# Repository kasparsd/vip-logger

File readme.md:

# Voltage, Current and Power Logger for Electric Skateboards, Scooters and Bicycles

See [the wiki](https://github.com/kasparsd/vip-logger/wiki).

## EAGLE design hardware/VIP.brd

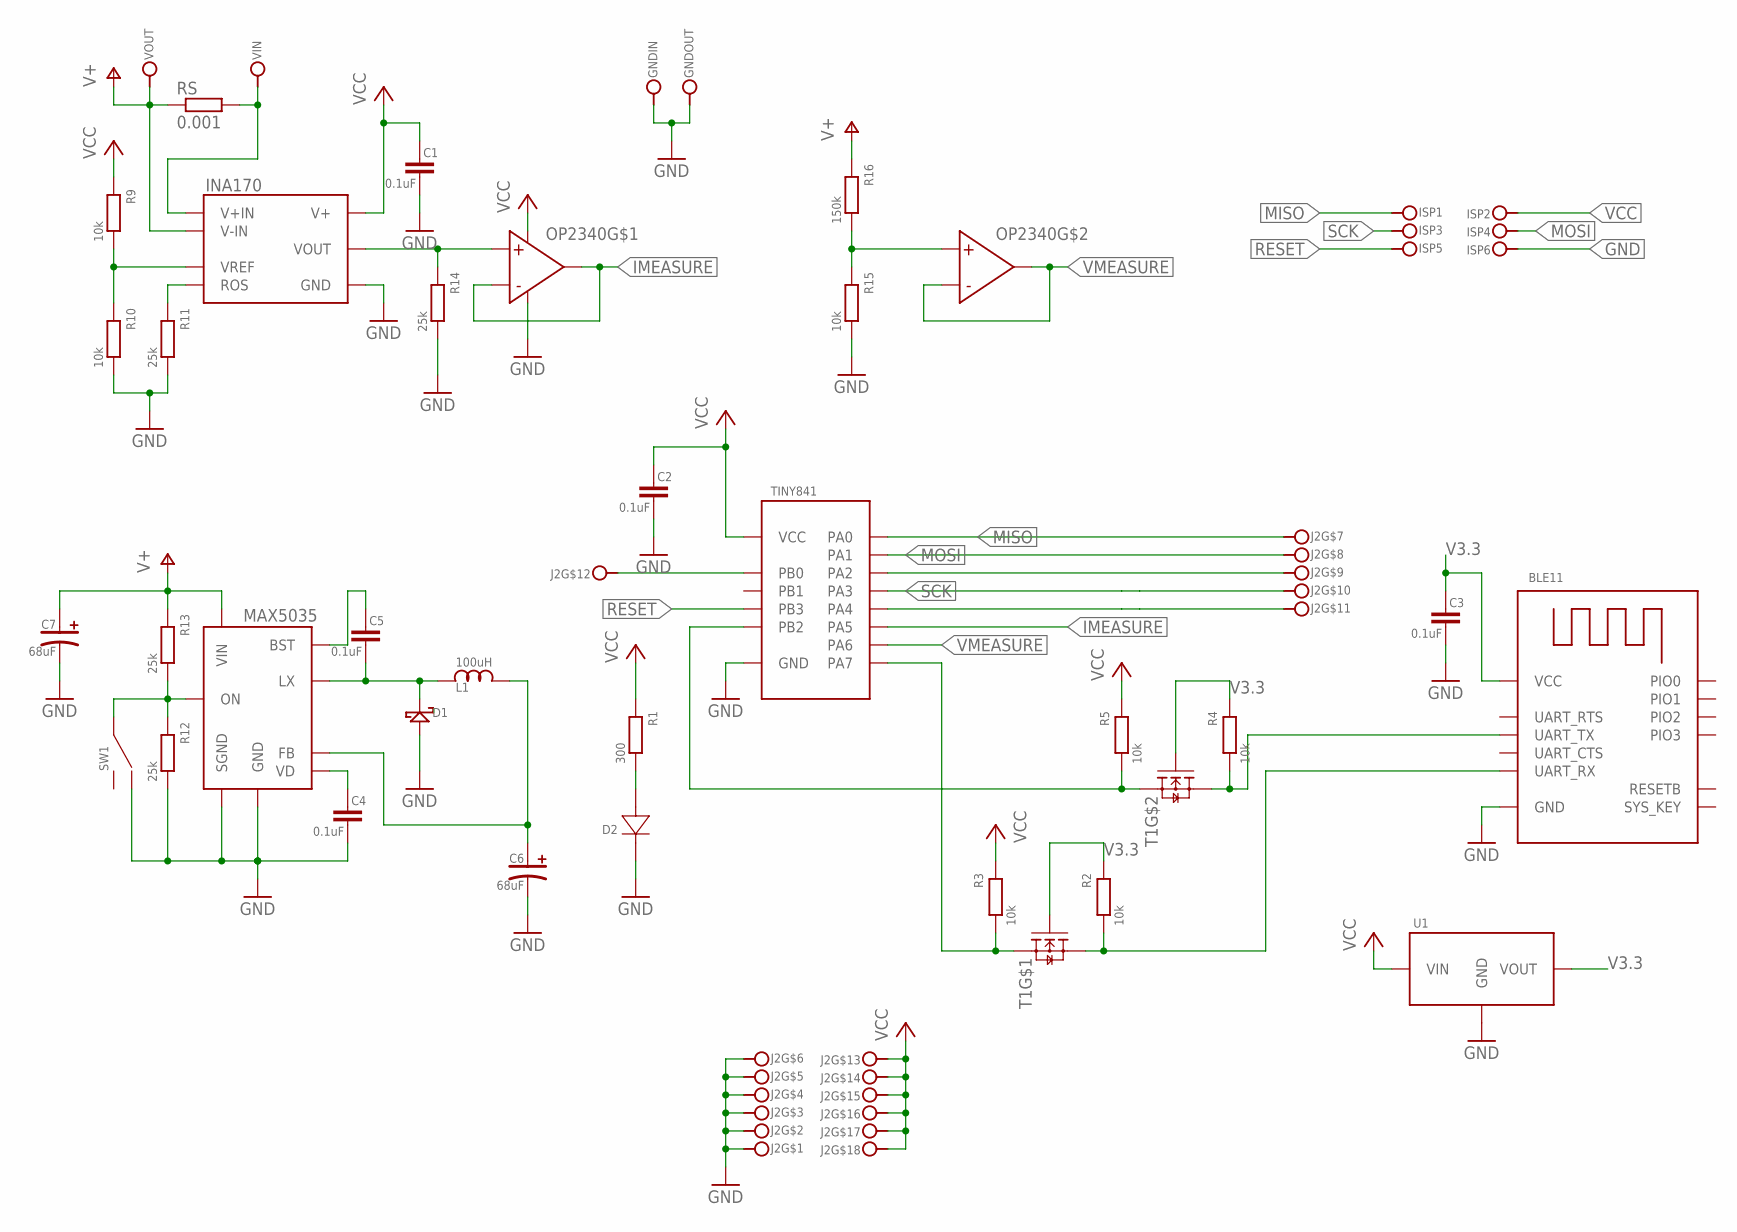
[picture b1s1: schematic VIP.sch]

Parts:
BLE11: HM-17BLE; HM17BLE
C1, C2, C3, C4, C5: 0.1uF; 0603L
C6: 68uF; RAD6.3MM
C7: 68uF; RAD12.5MM
D1: SCHOTTKY; DO-214AA
D2: SINGLELEDKP-3216SRC-PRV; LED3.2X1.6MM
GNDIN: POWERTAB; POWER8X10MM
GNDOUT: POWERTAB; POWER8X10MM
INA170: INA170
ISP: CON254_6WAY254-2X3-EDGE; CON254MM08_2X3_EDGE
J2: CON254_18WAY3X6; CON254MM08_3X6
L1: 100uH; SRN8040
MAX5035: MAX5035; NSOIC-8
OP2340: OPA2340; SO-8
R1: 300; 0603L
R2, R3, R4, R5, R9, R10, R15: 10k; 0603L
R11, R12, R13, R14: 25k; 0603L
R16: 150k; 0603L
RS: 0.001; 3921[1052METRIC]
SW1: SWITCH-1P2T; JS102011
T1: 2N7002; SOT-563
TINY841: ATTINY841; SOIC14
U1: L78L33A; SOT-89
VIN: POWERTAB; POWER8X10MM
VOUT: POWERTAB; POWER8X10MM

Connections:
GND: BLE11.P$12 (GND), C1.P$2, C2.P$2, C3.P$2, C4.P$2, C6.P$2, C7.P$2, D1.P$2 (A), D2.P$2 (K), GNDIN.P$1, GNDOUT.P$1, INA170.P$4 (GND), ISP.P$6, J2.P$1, J2.P$2, J2.P$3, J2.P$4, J2.P$5, J2.P$6, MAX5035.P$3 (SGND), MAX5035.P$6 (GND), OP2340.P$4 (V-), R10.P$2, R11.P$2, R12.P$2, R14.P$2, R15.P$2, SW1.P$1, TINY841.P$14 (GND), U1.P$2 (GND)
IMEASURE: OP2340.P$1 (OUT), OP2340.P$2 (IN-), TINY841.P$8 (PA5)
MISO: ISP.P$1, J2.P$7, TINY841.P$13 (PA0)
MOSI: ISP.P$4, J2.P$8, TINY841.P$12 (PA1)
unnamed: MAX5035.P$5 (ON), R12.P$1, R13.P$2, SW1.P$2
unnamed: INA170.P$6 (VOUT), OP2340.P$3 (IN+), R14.P$1
unnamed: INA170.P$5 (ROS), R11.P$1
unnamed: INA170.P$3 (VREF), R9.P$2, R10.P$1
unnamed: C4.P$1, MAX5035.P$2 (VD)
unnamed: INA170.P$2 (V+IN), RS.P$2 (2), VIN.P$1
unnamed: C5.P$2, D1.P$1 (C), L1.P$1, MAX5035.P$8 (LX)
unnamed: C5.P$1, MAX5035.P$1 (BST)
unnamed: J2.P$9, TINY841.P$11 (PA2)
unnamed: OP2340.P$5 (IN+), R15.P$1, R16.P$2
unnamed: C6.P$1, L1.P$2, MAX5035.P$4 (FB)
unnamed: J2.P$11, TINY841.P$9 (PA4)
unnamed: D2.P$1 (A), R1.P$2
unnamed: J2.P$12, TINY841.P$2 (PB0)
unnamed: R3.P$2, T1.P$4 (S), TINY841.P$6 (PA7)
unnamed: BLE11.P$2 (UART_TX), R4.P$2, T1.P$6 (D)
unnamed: BLE11.P$4 (UART_RX), R2.P$2, T1.P$3 (D)
RESET: ISP.P$5, TINY841.P$4 (PB3)
SCK: ISP.P$3, J2.P$10, TINY841.P$10 (PA3)
TOAT: R5.P$2, T1.P$1 (S), TINY841.P$5 (PB2)
V3.3: BLE11.P$9 (VCC), C3.P$1, R2.P$1, R4.P$1, T1.P$2 (G), T1.P$5 (G), U1.P$1 (VOUT)
V+: C7.P$1, INA170.P$1 (V-IN), MAX5035.P$7 (VIN), R13.P$1, R16.P$1, RS.P$1 (1), VOUT.P$1
VCC: C1.P$1, C2.P$1, INA170.P$8 (V+), ISP.P$2, J2.P$13, J2.P$14, J2.P$15, J2.P$16, J2.P$17, J2.P$18, OP2340.P$8 (V+), R1.P$1, R3.P$1, R5.P$1, R9.P$1, TINY841.P$1 (VCC), U1.P$3 (VIN)
VMEASURE: OP2340.P$6 (IN-), OP2340.P$7 (OUT), TINY841.P$7 (PA6)

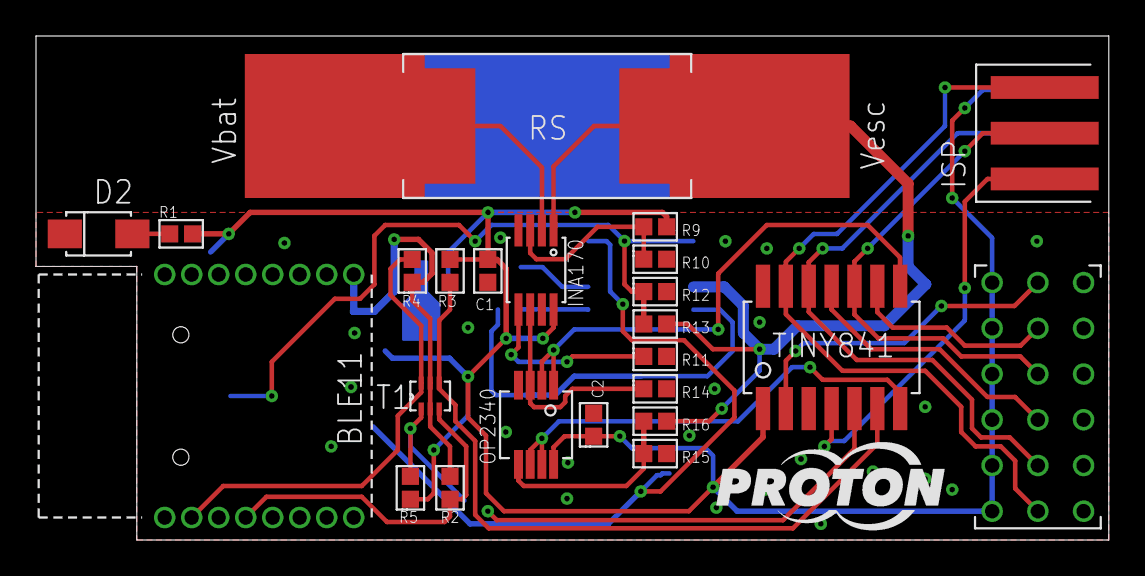
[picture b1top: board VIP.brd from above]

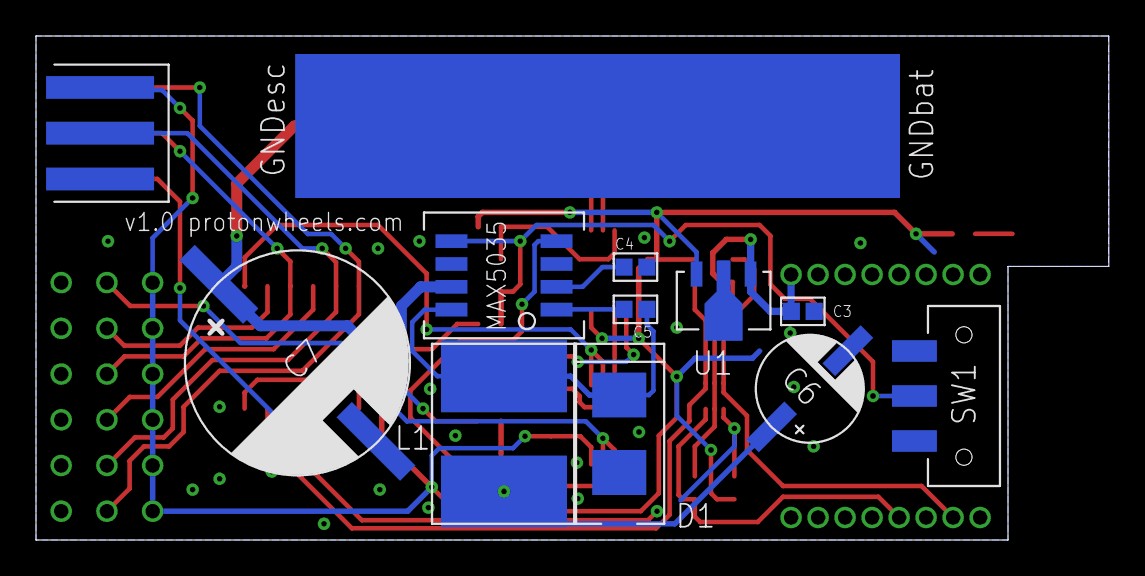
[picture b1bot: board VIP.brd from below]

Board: 2 copper layers, 59.6 x 28.0 mm, 38 parts (12 on the bottom side), 28 nets.

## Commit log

2016-08-22 Ignore Eagle backups
2016-08-22 Add the hardware readme
2016-08-22 Add firmware
2016-09-03 Add component datasheets
2016-09-18 Remove the old file
2016-09-18 Ignore system files
